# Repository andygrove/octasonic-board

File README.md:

# Octasonic 8 x HC-SR04 Breakout Board

For full documentation, please see: https://theotherandygrove.com/octasonic/

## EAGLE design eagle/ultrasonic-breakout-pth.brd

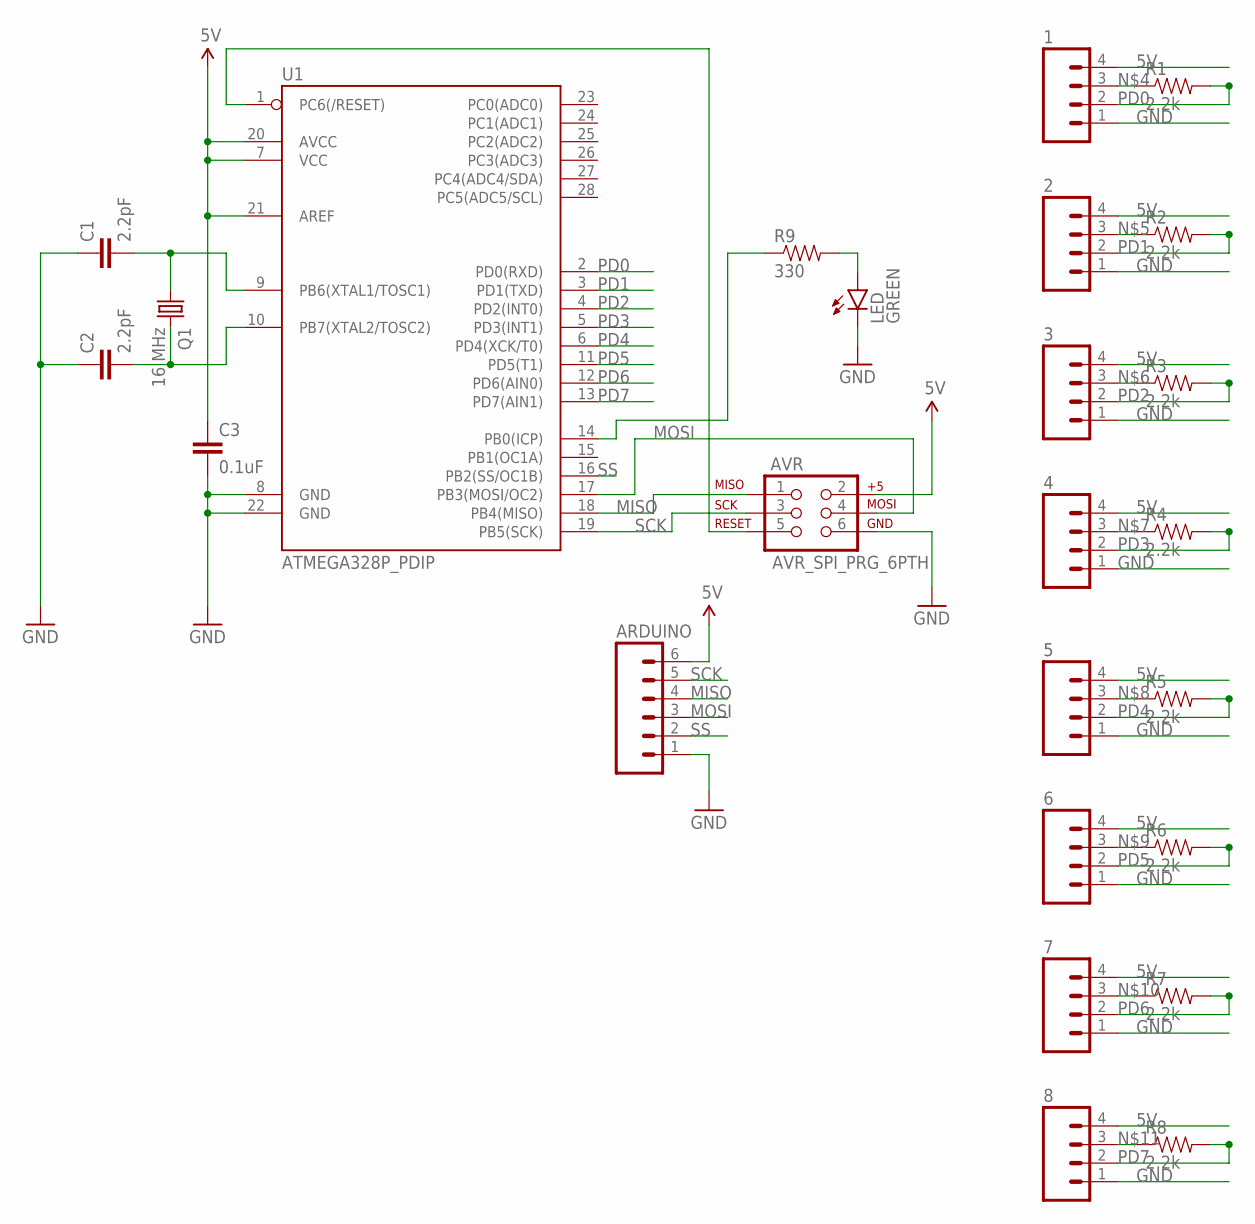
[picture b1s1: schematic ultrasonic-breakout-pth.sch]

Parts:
1, 2, 3, 4, 5, 6, 7, 8: M04LOCK; 1X04_LOCK
ARDUINO: M06LOCK; 1X06_LOCK
AVR: AVR_SPI_PRG_6PTH; 2X3
C1, C2: 2.2pF; CAP-PTH-SMALL
C3: 0.1uF; CAP-PTH-5MM
LED: GREEN; LED5MM
Q1: 16 MHz; HC49U-V
R1, R2, R3, R4, R5, R6, R7, R8: 2.2k; AXIAL-0.4
R9: 330; AXIAL-0.4
U1: ATMEGA328P_PDIP; DIL28-3

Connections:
5V: 1.4, 2.4, 3.4, 4.4, 5.4, 6.4, 7.4, 8.4, ARDUINO.6, AVR.2, C3.1, U1.7 (VCC), U1.20 (AVCC), U1.21 (AREF)
GND: 1.1, 2.1, 3.1, 4.1, 5.1, 6.1, 7.1, 8.1, ARDUINO.1, AVR.6, C1.1, C2.1, C3.2, LED.K (C), U1.8 (GND), U1.22 (GND)
MISO: ARDUINO.4, AVR.1, U1.18 (PB4(MISO))
MOSI: ARDUINO.3, AVR.4, U1.17 (PB3(MOSI/OC2))
unnamed: C1.2, Q1.1, U1.9 (PB6(XTAL1/TOSC1))
unnamed: AVR.5, U1.1 (PC6(/RESET))
unnamed: C2.2, Q1.2, U1.10 (PB7(XTAL2/TOSC2))
unnamed: 1.3, R1.P$1 (1)
unnamed: 2.3, R2.P$1 (1)
unnamed: 3.3, R3.P$1 (1)
unnamed: 4.3, R4.P$1 (1)
unnamed: 5.3, R5.P$1 (1)
unnamed: 6.3, R6.P$1 (1)
unnamed: 7.3, R7.P$1 (1)
unnamed: 8.3, R8.P$1 (1)
unnamed: R9.P$1 (1), U1.14 (PB0(ICP))
unnamed: LED.A, R9.P$2 (2)
PD0: 1.2, R1.P$2 (2), U1.2 (PD0(RXD))
PD1: 2.2, R2.P$2 (2), U1.3 (PD1(TXD))
PD2: 3.2, R3.P$2 (2), U1.4 (PD2(INT0))
PD3: 4.2, R4.P$2 (2), U1.5 (PD3(INT1))
PD4: 5.2, R5.P$2 (2), U1.6 (PD4(XCK/T0))
PD5: 6.2, R6.P$2 (2), U1.11 (PD5(T1))
PD6: 7.2, R7.P$2 (2), U1.12 (PD6(AIN0))
PD7: 8.2, R8.P$2 (2), U1.13 (PD7(AIN1))
SCK: ARDUINO.5, AVR.3, U1.19 (PB5(SCK))
SS: ARDUINO.2, U1.16 (PB2(SS/OC1B))

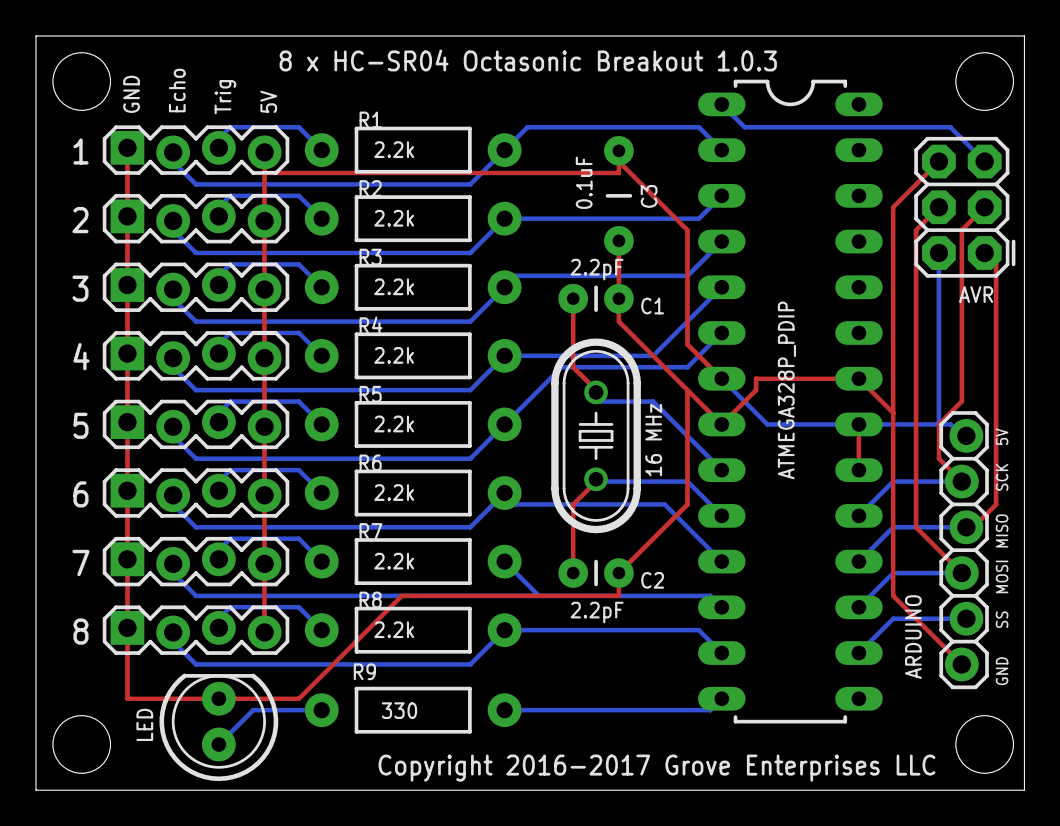
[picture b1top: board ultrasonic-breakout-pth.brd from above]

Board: 2 copper layers, 54.9 x 41.9 mm, 25 parts (0 on the bottom side), 27 nets.

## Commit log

2015-12-13 set up project structure
2015-12-13 rough out master/slave
2015-12-13 save
2015-12-13 rename folders
2015-12-13 SPI working between Arduino master and AVR slave
2015-12-13 change fuse bits for 16 MHz
2015-12-13 remove avr-master
2015-12-15 implements get/set sensor count protocol
2015-12-15 slave with interrupts is working, but clock divider is wrong (counting 16x too fast)
2015-12-16 reading sensor and reporting results
2015-12-16 single pin for sensor
2015-12-16 can now read 6 sensors
2015-12-16 can now read 8 sensors on port D
2015-12-16 initial board layout
2016-01-10 improve board layout
2016-01-24 fixed missing SS connection in schematic, also switched to 5mm capacitor and completely redesigned board layout
2016-01-24 refining board layout
2016-01-24 add v1 of smd layout .. is missing SS connection
2016-01-24 changed first connecter to swap trig/echo
2016-01-24 finished swapping trig/echo on all connectors
2016-02-06 Fix error on board (AVR ISP did not have SCK routed)
2016-03-04 change branding on board
2016-09-03 sleep 50 ms between readings, time out at 200 cm
2017-05-10 update board to use locking molex connectors
2018-01-18 remove everything except board design (code has moved to other repos)
2023-11-03 add kicad board
2023-11-04 latest
2023-11-04 rename

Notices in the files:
eagle/ultrasonic-breakout-pth.brd:
Copyright 2016-2017 Grove Enterprises LLC
parts and their libraries:
SparkFun-Connectors: Licensing: Creative Commons ShareAlike 4.0 International - https://creativecommons.org/licenses/by-sa/4.0
